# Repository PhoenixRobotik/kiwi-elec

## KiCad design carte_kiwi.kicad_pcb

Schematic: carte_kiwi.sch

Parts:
C1, C2, C9, C10: 100nF; C_0805_HandSoldering
C3, C4: 10uF; C_0805_HandSoldering
C5: 0.1µF; C_0805_HandSoldering
C6: 10nF; C_0805_HandSoldering
C7: 1uF; C_0805_HandSoldering
C8: 4.7uF; C_0805_HandSoldering
D1, D2, D3: D_Zener_Small; D_SOD-123
D4: LED PWR; LED_0805
D5: LED ACTIVITY; LED_0805
D6: LED STATUS; LED_0805
IC1: MCP2562; SOIC-8_3.9x4.9mm_Pitch1.27mm
P1, P3: CONN_01X05; JST_XH_B05B-XH-A_05x2.50mm_Straight
P2, P4, P7, P8: CONN_01X03; Pin_Header_Straight_1x03
P5: Serial Wire; Pin_Header_Straight_1x06
P6, P9: CAN_conn; JST_XH_B04B-XH-A_04x2.50mm_Straight
R1, R2, R3, R4, R7, R8, R9, R10: R; R_0805_HandSoldering
R5, R6: 0R; R_0805_HandSoldering
SW1: SW_Push; SW_SPST_EVQPE1
U1: LD1117S50TR; SOT-223-3Lead_TabPin2
U2: LD1117S33TR; SOT-223-3Lead_TabPin2
U3: STM32F303K8; LQFP-32_7x7mm_Pitch0.8mm

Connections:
+3V3: C4.1, C6.1, C7.1, C8.1, C9.1, C10.1, IC1.5 (VIO), P5.1, R4.1, R5.1, R9.1, U2.2 (VO), U3.1 (VDD), U3.5 (VDDA/VREF+), U3.17 (VDD)
+5V: C2.1, C3.1, IC1.3 (VDD), R6.1, U1.2 (VO), U2.3 (VI)
+9V: C1.1, P6.4 (GND), P9.4 (GND), U1.3 (VI)
ACTIVITY_LED: R7.1, U3.2 (PF0)
BOOT0: R9.2, R10.1, U3.31 (BOOT0)
CAN_H: IC1.7 (CANH), P6.2 (CAN_H), P9.2 (CAN_H)
CAN_L: IC1.6 (CANL), P6.3 (CAN_L), P9.3 (CAN_L)
CAN_RX: IC1.4 (RXD), U3.21 (PA11)
CAN_TX: IC1.1 (TXD), U3.22 (PA12)
GND: C1.2, C2.2, C3.2, C4.2, C5.2, C6.2, C7.2, C8.2, C9.2, C10.2, D1.2, D2.2, D3.2, D4.1 (K), D5.1 (K), D6.1 (K), IC1.2 (VSS), IC1.8 (STBY), P1.1, P2.1, P3.1, P4.1, P5.3, P6.1 (VCC), P7.1, P8.1, P9.1 (VCC), R10.2, SW1.2, U1.1 (GND), U2.1 (GND), U3.16 (VSS), U3.32 (VSS)
NRST: C5.1, P5.5, SW1.1, U3.4 (NRST)
unnamed: D4.2 (A), R4.2
unnamed: D5.2 (A), R7.2
unnamed: D6.2 (A), R8.2
Protect1: P1.4, R1.2
Protect2: P1.3, R2.2
Protect3: P1.2, R3.2
STATUS_LED: R8.1, U3.3 (PF1)
SWCLK: P5.2, U3.24 (PA14)
SWDIO: P5.4, U3.23 (PA13)
Sensor_PWR: P1.5, P3.5, R5.2, R6.2
TIM1|ENCA/Hall1: P3.4, U3.18 (PA8)
TIM1|ENCB/Hall2: P3.3, U3.19 (PA9)
TIM1|Hall3: P3.2, U3.20 (PA10)
TIM2|ENCA/Hall1: D1.1, R1.1, U3.6 (PA0)
TIM2|ENCB/Hall2: D2.1, R2.1, U3.7 (PA1)
TIM2|Hall3: D3.1, R3.1, U3.8 (PA2)
TIM3|DIR1/PWM2: P2.2, U3.13 (PA7)
TIM3|DIR2/PWM4: P4.2, U3.15 (PB1)
TIM3|PWM1: P2.3, U3.12 (PA6)
TIM3|PWM3: P4.3, U3.14 (PB0)
USART1_RX/SDA: P7.2, U3.30 (PB7)
USART1_TX/SCL: P7.3, U3.29 (PB6)
USART2_RX: P8.2, U3.27 (PB4)
USART2_TX/SWO: P5.6, P8.3, U3.26 (PB3)

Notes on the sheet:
Main Flash
Bootloader
Choice must be done between R3 or R4
Allow choice between 3.3V or 5V
Decoupling capacitor analog
Decoupling capacitor digital

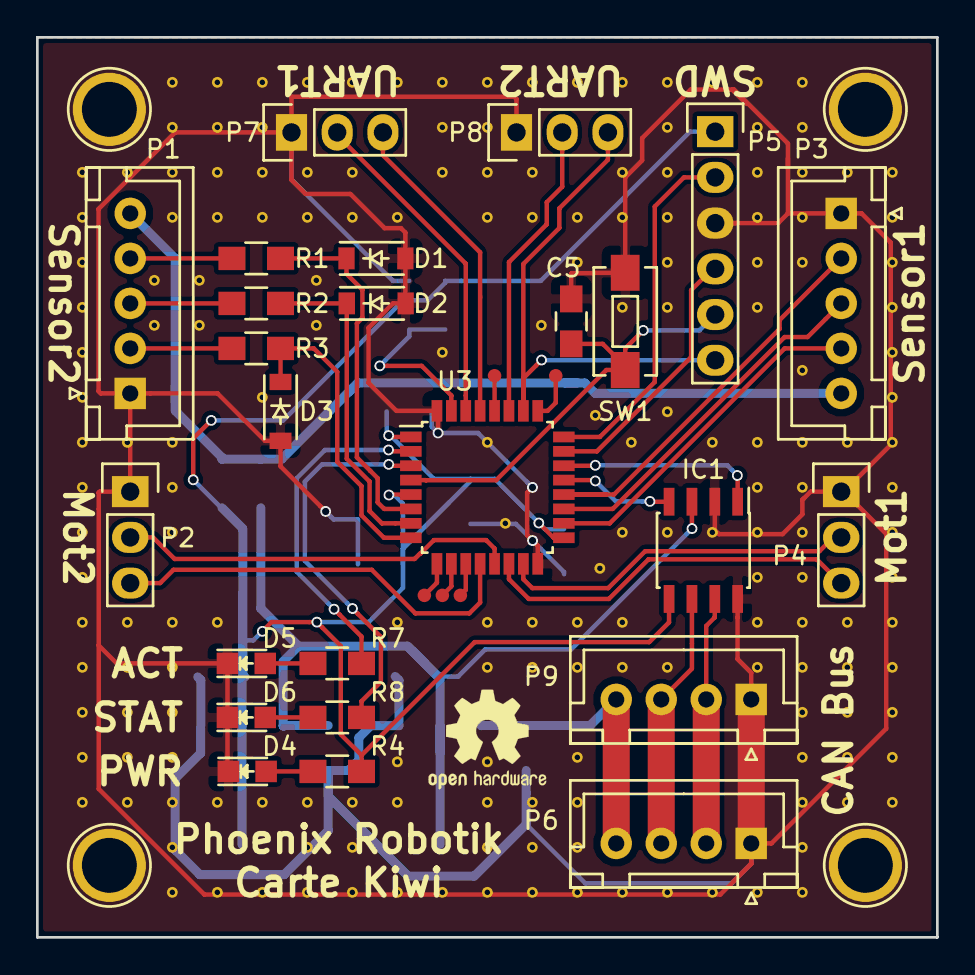
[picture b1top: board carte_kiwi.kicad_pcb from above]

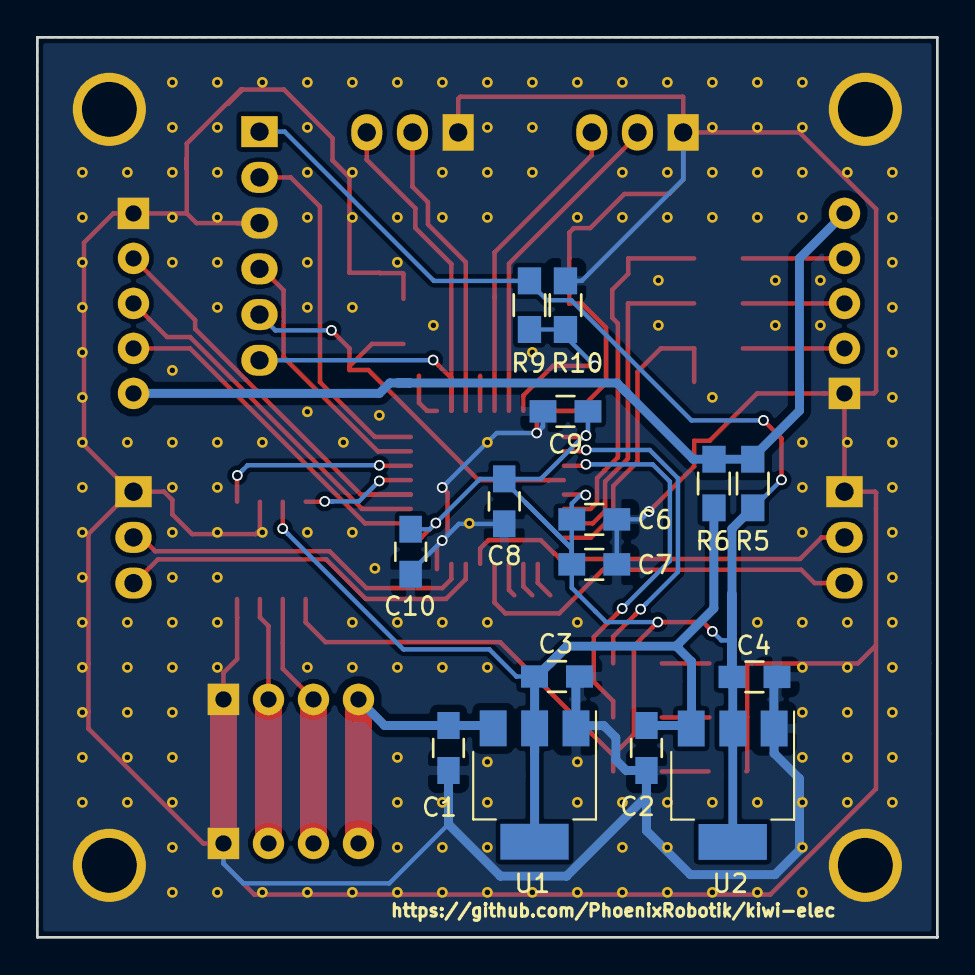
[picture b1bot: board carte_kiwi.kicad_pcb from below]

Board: 2 copper layers, 50.0 x 50.0 mm, 40 parts (15 on the bottom side), 35 nets.

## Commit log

2017-02-11 association emprunte + correction erreurs
2017-02-11 préplacement des composants
2017-02-11 ajoute capa découplage
2017-02-11 correction inversion SCL et SDA + évite renomage systématique des nets GND en NC
2017-02-11 routage terminé mais à nettoyer
2017-02-11 retire les connexions à GND des pins non utilisées
2017-02-11 fix gitignore + lib path
2017-02-11 Mise à jour des libs (zener, led, switch)
2017-02-12 corrige erreurs ERC
2017-02-12 retourné connecteur CAN
2017-02-13 change de coté les capa de découplage et arrange un peu les choses
2017-02-13 ajoute les trou de vis et suprime les drawings de placement
2017-02-13 ajoute via de connection entre plans de masse
2017-02-15 add test points on unused pins
2017-02-15 améliore un peu ?
2017-02-15 bouge le transceiver CAN pour simplifier le routage
2017-02-15 ameliore masse
2017-02-15 déplace certaines ref
2017-02-15 met les ref arrières dans le même sens et améliore un peu
2017-02-16 ajout nom, url et export gerber
2017-02-16 added OpenHW logo
2017-02-16 correct OSHW logo
2017-03-12 updated footprint
2017-04-23 add TODO
2017-04-28 invert C2 and C3 places (+ move U1 and U2 references)
2018-05-23 First changes to schema. TODO : use phoenixrobotik specific libs for can_conn
